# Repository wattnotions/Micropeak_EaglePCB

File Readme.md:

!
!

PDF of schematic available  [here](schematic.pdf)

Digikey basket with all components available here: https://www.digikey.ie/short/rqj3081d

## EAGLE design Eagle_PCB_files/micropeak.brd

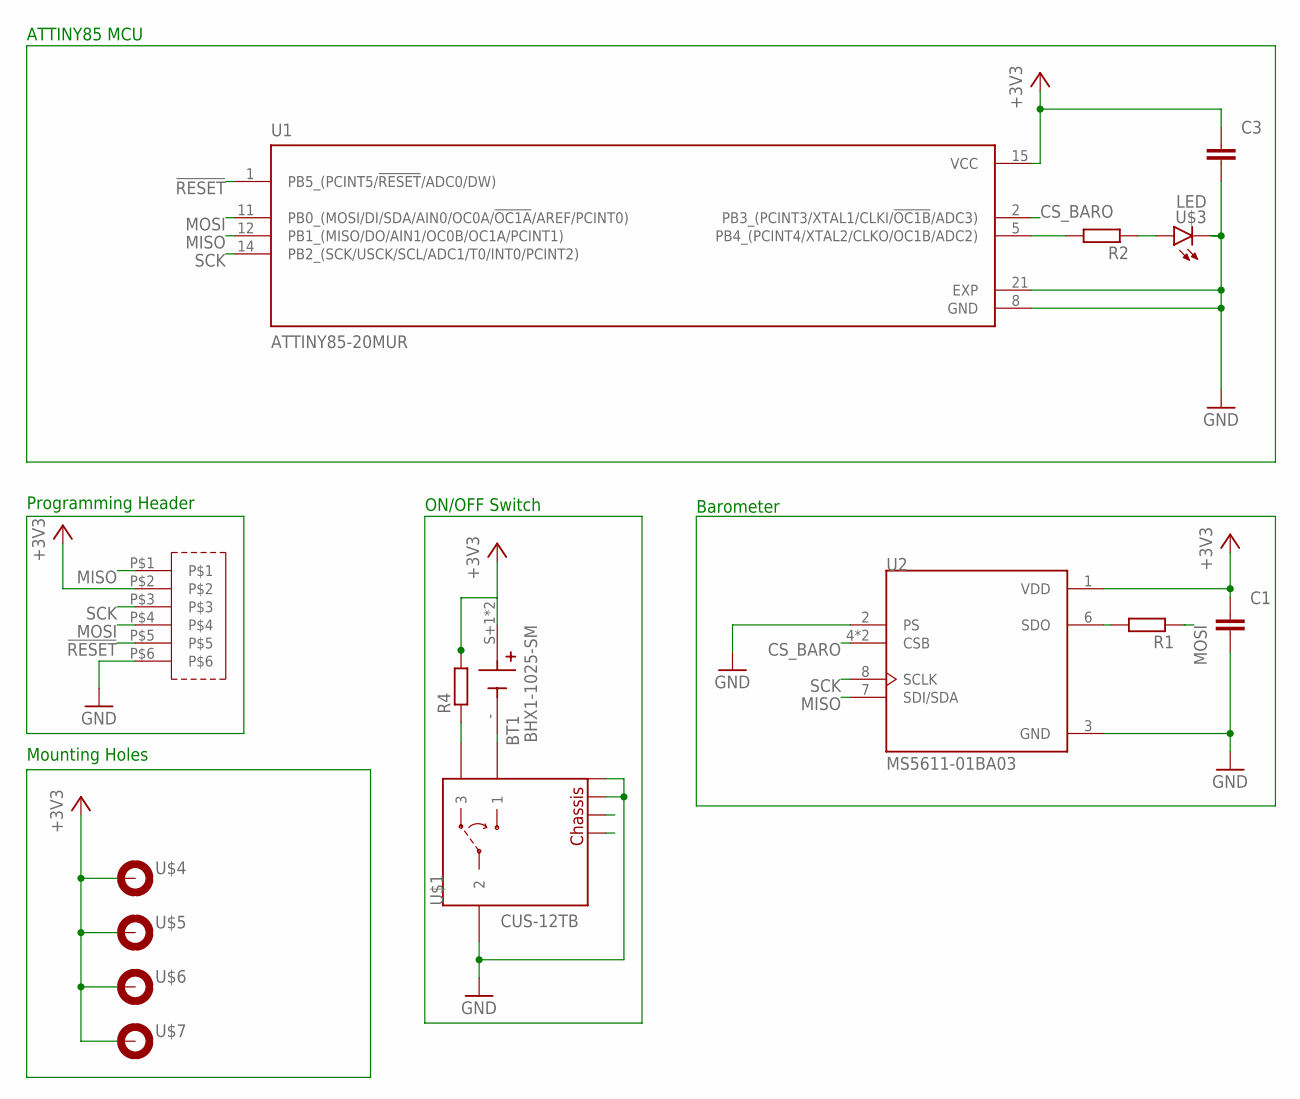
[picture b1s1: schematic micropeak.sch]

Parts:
BT1: BHX1-1025-SM; BAT_BHX1-1025-SM
C1, C3: C-EUC0402; C0402
R1, R2, R4: R-EU_R0402; R0402
U1: ATTINY85-20MUR; QFN50P400X400X80-21N
U2: MS5611-01BA03; SON125P500X300X100-8N
U$1: CUS-12TB; CUS-12B
U$2: 1X6_PROG_HEADER; 1X6_SMD_HEADER_PADS
U$3: LED; LED_LYT68B-T2V1-26-Z
U$4, U$5, U$6, U$7: MOUNT_HOLE; 2,8-PAD

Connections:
!RESET!: U1.1 (PB5_(PCINT5/!RESET!/ADC0/DW)), U$2.P$5
+3V3: BT1.S+1 (+), BT1.S+2 (+), C1.1, C3.1, R4.2, U1.15 (VCC), U2.1 (VDD), U$2.P$2, U$4.B2,8, U$5.B2,8, U$6.B2,8, U$7.B2,8
CS_BARO: U1.2 (PB3_(PCINT3/XTAL1/CLKI/!OC1B!/ADC3)), U2.4 (CSB), U2.5 (CSB)
GND: C1.2, C3.2, U1.8 (GND), U1.21 (EXP), U2.2 (PS), U2.3 (GND), U$1.P$2 (2), U$1.P$4 (GND), U$1.P$5 (GND), U$2.P$6, U$3.C
MISO: U1.12 (PB1_(MISO/DO/AIN1/OC0B/OC1A/PCINT1)), U2.7 (SDI/SDA), U$2.P$1
MOSI: R1.1, U1.11 (PB0_(MOSI/DI/SDA/AIN0/OC0A/!OC1A!/AREF/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), U$2.P$4
unnamed: BT1.-, U$1.P$1 (1)
unnamed: R4.1, U$1.P$3 (3)
unnamed: R2.2, U1.5 (PB4_(PCINT4/XTAL2/CLKO/OC1B/ADC2))
unnamed: R2.1, U$3.A
unnamed: R1.2, U2.6 (SDO)
SCK: U1.14 (PB2_(SCK/USCK/SCL/ADC1/T0/INT0/PCINT2)), U2.8 (SCLK), U$2.P$3

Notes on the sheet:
ATTINY85 MCU
Programming Header
ON/OFF Switch
Barometer
Mounting Holes

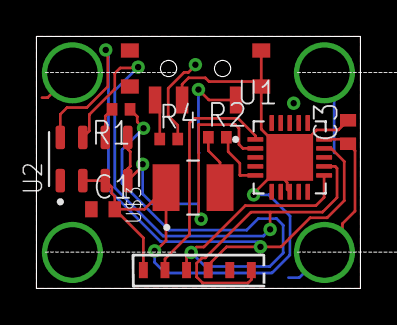
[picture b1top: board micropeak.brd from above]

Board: 2 copper layers, 18.0 x 14.0 mm, 15 parts (1 on the bottom side), 12 nets.

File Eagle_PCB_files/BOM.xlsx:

MFG Part Num | Digikey Part Number | Quantity | Description
LO T67K-K1L2-24-Z | 475-2745-1-ND | 1 | 2-PLCC Orange LED
BHX1-1025-SM | BHX1-1025-SM-ND | 1 | 10mm coin cell battery holder
CUS-12TB | 563-1102-1-ND | 1 | ON/OFF switch
ATTINY85-20MUR | ATTINY85-20MURCT-ND | 1 | Attiny85 MCU QFN package
MS561101BA03-50 | 223-1622-1-ND | 1 | Barometric pressure sensor

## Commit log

2023-01-22 image of micropeak schematic from geda-gschem
2023-01-23 found micropeak fw - changed folder structure
2023-01-23 moved images folder
2023-01-23 added attiny 85 sym and fp
2023-01-23 added power switch sym and fp
2023-01-23 added BOM
2023-01-23 added schematic sheet template
2023-01-23 updated on/off switch sym to make spdt layout clearer
2023-01-23 added prog header sym
2023-01-23 prog header smd pad size worked out as 0.9x1.2mm
2023-01-23 pitch 1.7mm
2023-01-23 schematic done
2023-01-23 scaled board image incorrecly, smd pads actually 0.5x0.9mm
2023-01-23 updated bom with correct LED
2023-01-23 replaced mounting holes with correct size hole
2023-01-23 fixed incorrect prog header pad sizes
2023-01-23 made 18x14mm board outline
2023-01-23 prelim floorplanning started
2023-01-24 added correct led datasheet
2023-01-24 have holes and outline positioned correctly - floorplanning done pretty much
2023-01-25 routing done
2023-01-25 test image to see if I can get it into readme
2023-01-25 updated readme with schematic pic
2023-01-25 updated readme trying to fix markup
2023-01-25 fixed typo in file name
2023-01-25 added gerbers
2023-01-25 added resistor values
2023-01-25 added backup files to gitignore
2023-01-25 deleted backup files
2023-01-25 updated readme with digikey basket
2023-01-25 added resistors and caps to BOM
